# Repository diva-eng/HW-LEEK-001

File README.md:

# Leek PCB Keychain

A small-form-factor PCB keychain shaped like Hatsune Miku's iconic leek, designed as concert swag for Magical Mirai. Features green LEDs at the tip, white LEDs at the base, and multiple user-selectable lighting patterns driven by an ATtiny402.

---

## Features

- Leek-shaped PCB outline with keychain mounting hole
- 5x green LEDs (leek tip) + 2x white LEDs (base)
- 4 lighting patterns selectable via tactile button
- SPDT slide switch for hard power on/off
- CR1220 coin cell powered (~16 hours active runtime)
- Fully assembled by JLCPCB (SMT + THT)

## Hardware

| Comment | Designator | Footprint | LCSC | Quantity |
|---------|------------|-----------|------|----------|
| ATtiny402-SS | U1 | SOIC-8_3.9x4.9mm_P1.27mm | C2053235 | 1 |
| Battery_Cell | BT1 | BAT-SMD_MY-1220-03 | C964818 | 1 |
| C | C1 | C_0402_1005Metric | C1525 | 1 |
| LED | D6,D7 | LED_0603_1608Metric | C189306 | 2 |
| LED | D4,D5 | LED_0603_1608Metric | C5246833 | 2 |
| LED | D1,D2,D3 | LED_0805_2012Metric | C5355441 | 3 |
| R | R6,R7 | R_0402_1005Metric | C25076 | 2 |
| R | R1,R2,R3,R4,R5 | R_0402_1005Metric | C25104 | 5 |
| ~ | SW3 | SW-TH_K3-1296S-E1 | C128955 | 1 |
| ~ | SW4 | SW-SMD_4P-L5.1-W5.1-P3.70-LS6.5-TL_H1.5 | C318884 | 1 |
| Conn_01x03_Pin | J1 | JST_EH_S3B-EH_1x03_P2.50mm_Horizontal |  | 1 |

See the full design document for complete BOM, resistor values, and wiring details.

## Firmware

Written in Arduino IDE using [megaTinyCore](https://github.com/SpenceKonde/megaTinyCore).

**Board manager URL:**
```
http://drazzy.com/package_drazzy.com_index.json
```

**Board settings:**
- Board: `ATtiny402`
- Clock: Internal 32kHz
- Programmer: SerialUPDI or Microchip SNAP

## Programming

The ATtiny402 is programmed via UPDI using 3 pads on the PCB edge (GND, VCC, UPDI). The cheapest programmer is a CH340 USB-serial adapter with a 1kΩ resistor:

```
USB-Serial TX ── 1kΩ ── UPDI pad
USB-Serial RX ──────── UPDI pad
GND ────────────────── GND pad
```

## LED Patterns

| # | Name | Description |
|---|------|-------------|
| 1 | Slow Pulse | Both LEDs breathe in and out together |
| 2 | Alternate | Green and white flash in turns |
| 3 | Chase | Green → white → both → off, repeat |
| 4 | Heartbeat | Double-flash then long pause |

Press the pattern button to cycle. The selected pattern is saved to EEPROM and restored on next power-on.

## License

MIT — see [LICENSE](LICENSE)

---

*A [Diva Engineering](https://github.com/diva-eng) project.*

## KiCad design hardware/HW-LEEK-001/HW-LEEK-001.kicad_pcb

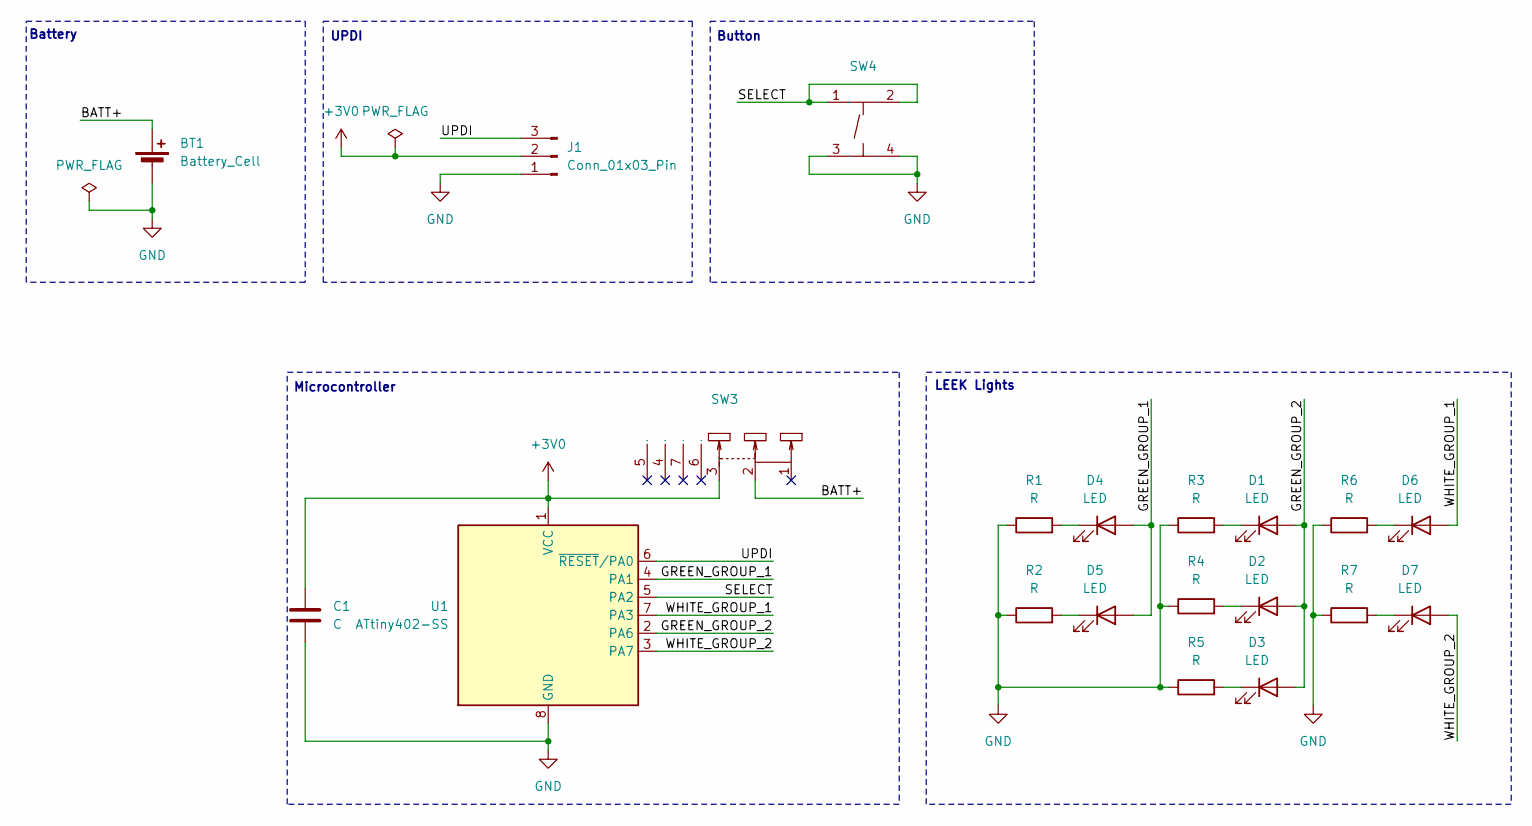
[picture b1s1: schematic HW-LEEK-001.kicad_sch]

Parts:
BT1: Battery_Cell; BAT-SMD_CR1220-2ZX; LCSC C964818
C1: C; C_0402_1005Metric; LCSC C1525
D1, D2, D3: LED; LED_0805_2012Metric; LCSC C5355441
D4, D5: LED; LED_0805_2012Metric; LCSC C5246833
D6, D7: LED; LED_0805_2012Metric; LCSC C189306
J1: Conn_01x03_Pin; JST_EH_S3B-EH_1x03_P2.50mm_Horizontal
R1, R2, R3, R4, R5: R; R_0402_1005Metric; LCSC C25104
R6, R7: R; R_0402_1005Metric; LCSC C25076
SW3: SW-TH_K3-1296S-E1; Manufacturer Part K3-1296S-E1; LCSC Part Name 卧贴双档 滑动开关
SW4: SW-SMD_4P-L5.1-W5.1-P3.70-LS6.5-TL_H1.5; Manufacturer Part TS-1187A-B-A-B; LCSC Part Name 5.1*5.1*1.5mm 立贴 轻触开关
U1: ATtiny402-SS; SOIC-8_3.9x4.9mm_P1.27mm; LCSC C2053235

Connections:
+3V0: C1.1, J1.2, SW3.3, U1.1 (VCC)
/BATT+: BT1.1 (+), SW3.2
/GREEN_GROUP_1: D4.2 (A), D5.2 (A), U1.4 (PA1)
/GREEN_GROUP_2: D1.2 (A), D2.2 (A), D3.2 (A), U1.2 (PA6)
/SELECT: SW4.1 (A), SW4.2 (B), U1.5 (PA2)
/UPDI: J1.3, U1.6 (~RESET/PA0)
/WHITE_GROUP_1: D6.2 (A), U1.7 (PA3)
/WHITE_GROUP_2: D7.2 (A), U1.3 (PA7)
GND: BT1.2 (-), C1.2, J1.1, R1.1, R2.1, R3.1, R4.1, R5.1, R6.1, R7.1, SW4.3 (C), SW4.4 (D), U1.8 (GND)
unnamed: D1.1 (K), R3.2
unnamed: D2.1 (K), R4.2
unnamed: D3.1 (K), R5.2
unnamed: D4.1 (K), R1.2
unnamed: D5.1 (K), R2.2
unnamed: D6.1 (K), R6.2
unnamed: D7.1 (K), R7.2

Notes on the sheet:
UPDI
Battery
LEEK Lights
Button
Microcontroller

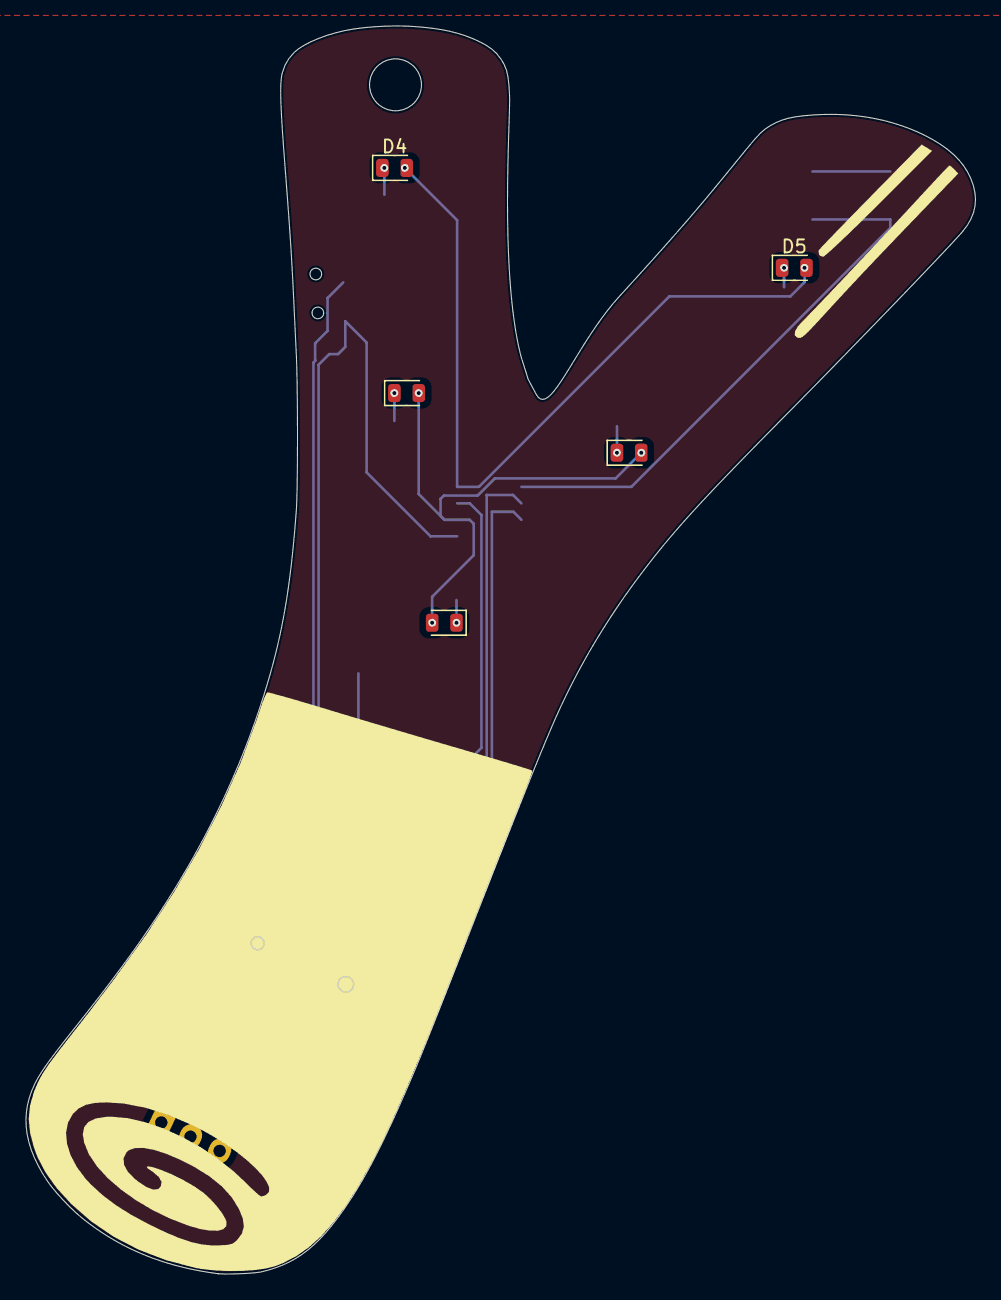
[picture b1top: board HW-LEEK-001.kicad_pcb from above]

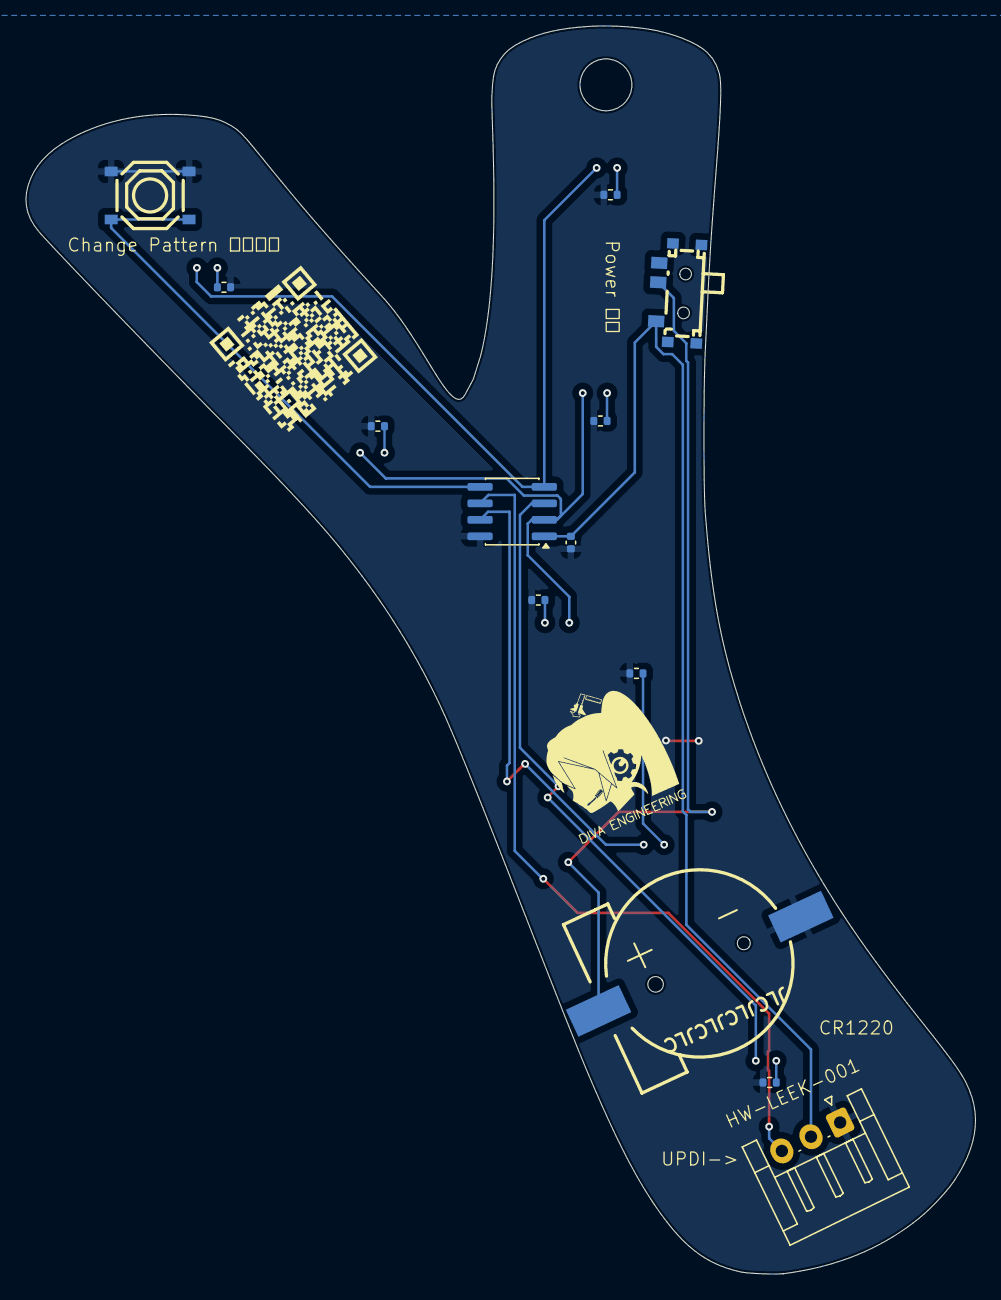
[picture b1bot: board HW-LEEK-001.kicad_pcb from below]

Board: 2 copper layers, 73.2 x 96.2 mm, 21 parts (13 on the bottom side), 16 nets.

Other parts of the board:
svg2mod: G***; leek

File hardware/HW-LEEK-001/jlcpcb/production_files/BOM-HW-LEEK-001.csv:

Comment,Designator,Footprint,LCSC,Quantity
ATtiny402-SS,U1,SOIC-8_3.9x4.9mm_P1.27mm,C2053235,1
Battery_Cell,BT1,BAT-SMD_CR1220-2ZX,C969906,1
C,C1,C_0402_1005Metric,C1525,1
LED,"D1,D2,D3,D4,D5",LED_0805_2012Metric,C5569446,5
LED,"D6,D7",LED_0805_2012Metric,C7280948,2
R,"R6,R7",R_0402_1005Metric,C25092,2
R,"R1,R2,R3,R4,R5",R_0402_1005Metric,C25104,5
~,SW3,SW-TH_K3-1296S-E1,C128955,1
~,SW4,SW-SMD_4P-L5.1-W5.1-P3.70-LS6.5-TL_H1.5,C318884,1
Conn_01x03_Pin,J1,JST_EH_S3B-EH_1x03_P2.50mm_Horizontal,,1

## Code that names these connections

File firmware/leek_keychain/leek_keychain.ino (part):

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 * PIN MAPPING (final PCB, from schematic)
 * ─────────────────────────────────────────────────────────────────────────────
 *
 *   PA0 / RESET  —  UPDI (programming only, do not use in firmware)
 *   PA1          —  GREEN_GROUP_1  — leek TIP        (2× green, topmost)
 *   PA2          —  SELECT button  — active LOW, internal pullup
 *   PA3          —  WHITE_GROUP_1  — below green group 2
 *   PA6          —  GREEN_GROUP_2  — 3× green, below tip
 *   PA7          —  WHITE_GROUP_2  — bottommost single LED
 *
 * ─────────────────────────────────────────────────────────────────────────────
 * PHYSICAL LED ORDER top → bottom
 * ─────────────────────────────────────────────────────────────────────────────
 *
 *   [1] GREEN_GROUP_1  PA1  — tip         (2× green)
 *   [2] GREEN_GROUP_2  PA6  — upper stalk (3× green)
 *   [3] WHITE_GROUP_1  PA3  — lower stalk (1× white)
 *   [4] WHITE_GROUP_2  PA7  — base        (1× white)
 *
 * ─────────────────────────────────────────────────────────────────────────────
 * ADDING A NEW PATTERN
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// HARDWARE PIN DEFINITIONS
// ═══════════════════════════════════════════════════════════════════════════════

#define PIN_TIP           PIN_PA1   // GREEN_GROUP_1 — leek tip       (2× green)
#define PIN_UPPER_STALK   PIN_PA6   // GREEN_GROUP_2 — upper stalk    (3× green)
#define PIN_LOWER_STALK   PIN_PA3   // WHITE_GROUP_1 — lower stalk    (1× white)
#define PIN_BASE          PIN_PA7   // WHITE_GROUP_2 — base           (1× white)
#define PIN_BUTTON        PIN_PA2   // SELECT button — active LOW

// ═══════════════════════════════════════════════════════════════════════════════
// CONFIGURATION
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
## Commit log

2026-03-09 Add MIT License to the project
2026-03-09 adding docs
2026-03-10 hardware revision 1
2026-03-17 HW Revision 02
2026-05-17 Update final hardware
